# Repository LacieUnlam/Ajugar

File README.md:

# Ajugar

<br>

Ajugar is an electronic circuit based on Makey Makey, but with an easy to build PCB in  KiCad. 
More info at [Ajugar web page](http://www.lacie-unlam.org/dokuwiki/doku.php?id=ajugar_publico).

AjugarV1
--------
  * First version. 
  * Validated in hardware.
  * Made with Kicad 2013.
  
AjugarV2
--------
  * Second version.
  * Cleaner design.
  * Made With Kicad 2015.
  * Not tested yet.

License Information
-------------------
The hardware is released under [Creative Commons ShareAlike 4.0 International](https://creativecommons.org/licenses/by-sa/4.0/).

Distributed as-is; no warranty is given.

You can find more information about them [here](http://www.lacie-unlam.org/).
Original Makey Makey:

  * [Make Makey in Sparkfun](https://www.sparkfun.com/products/11511).
  * [Makey Makey in Github](https://github.com/sparkfun/MaKeyMaKey).
  * [Local copy in this repo](./original/).

Makey Makey is a registered trademark of JoyLabz LLC.

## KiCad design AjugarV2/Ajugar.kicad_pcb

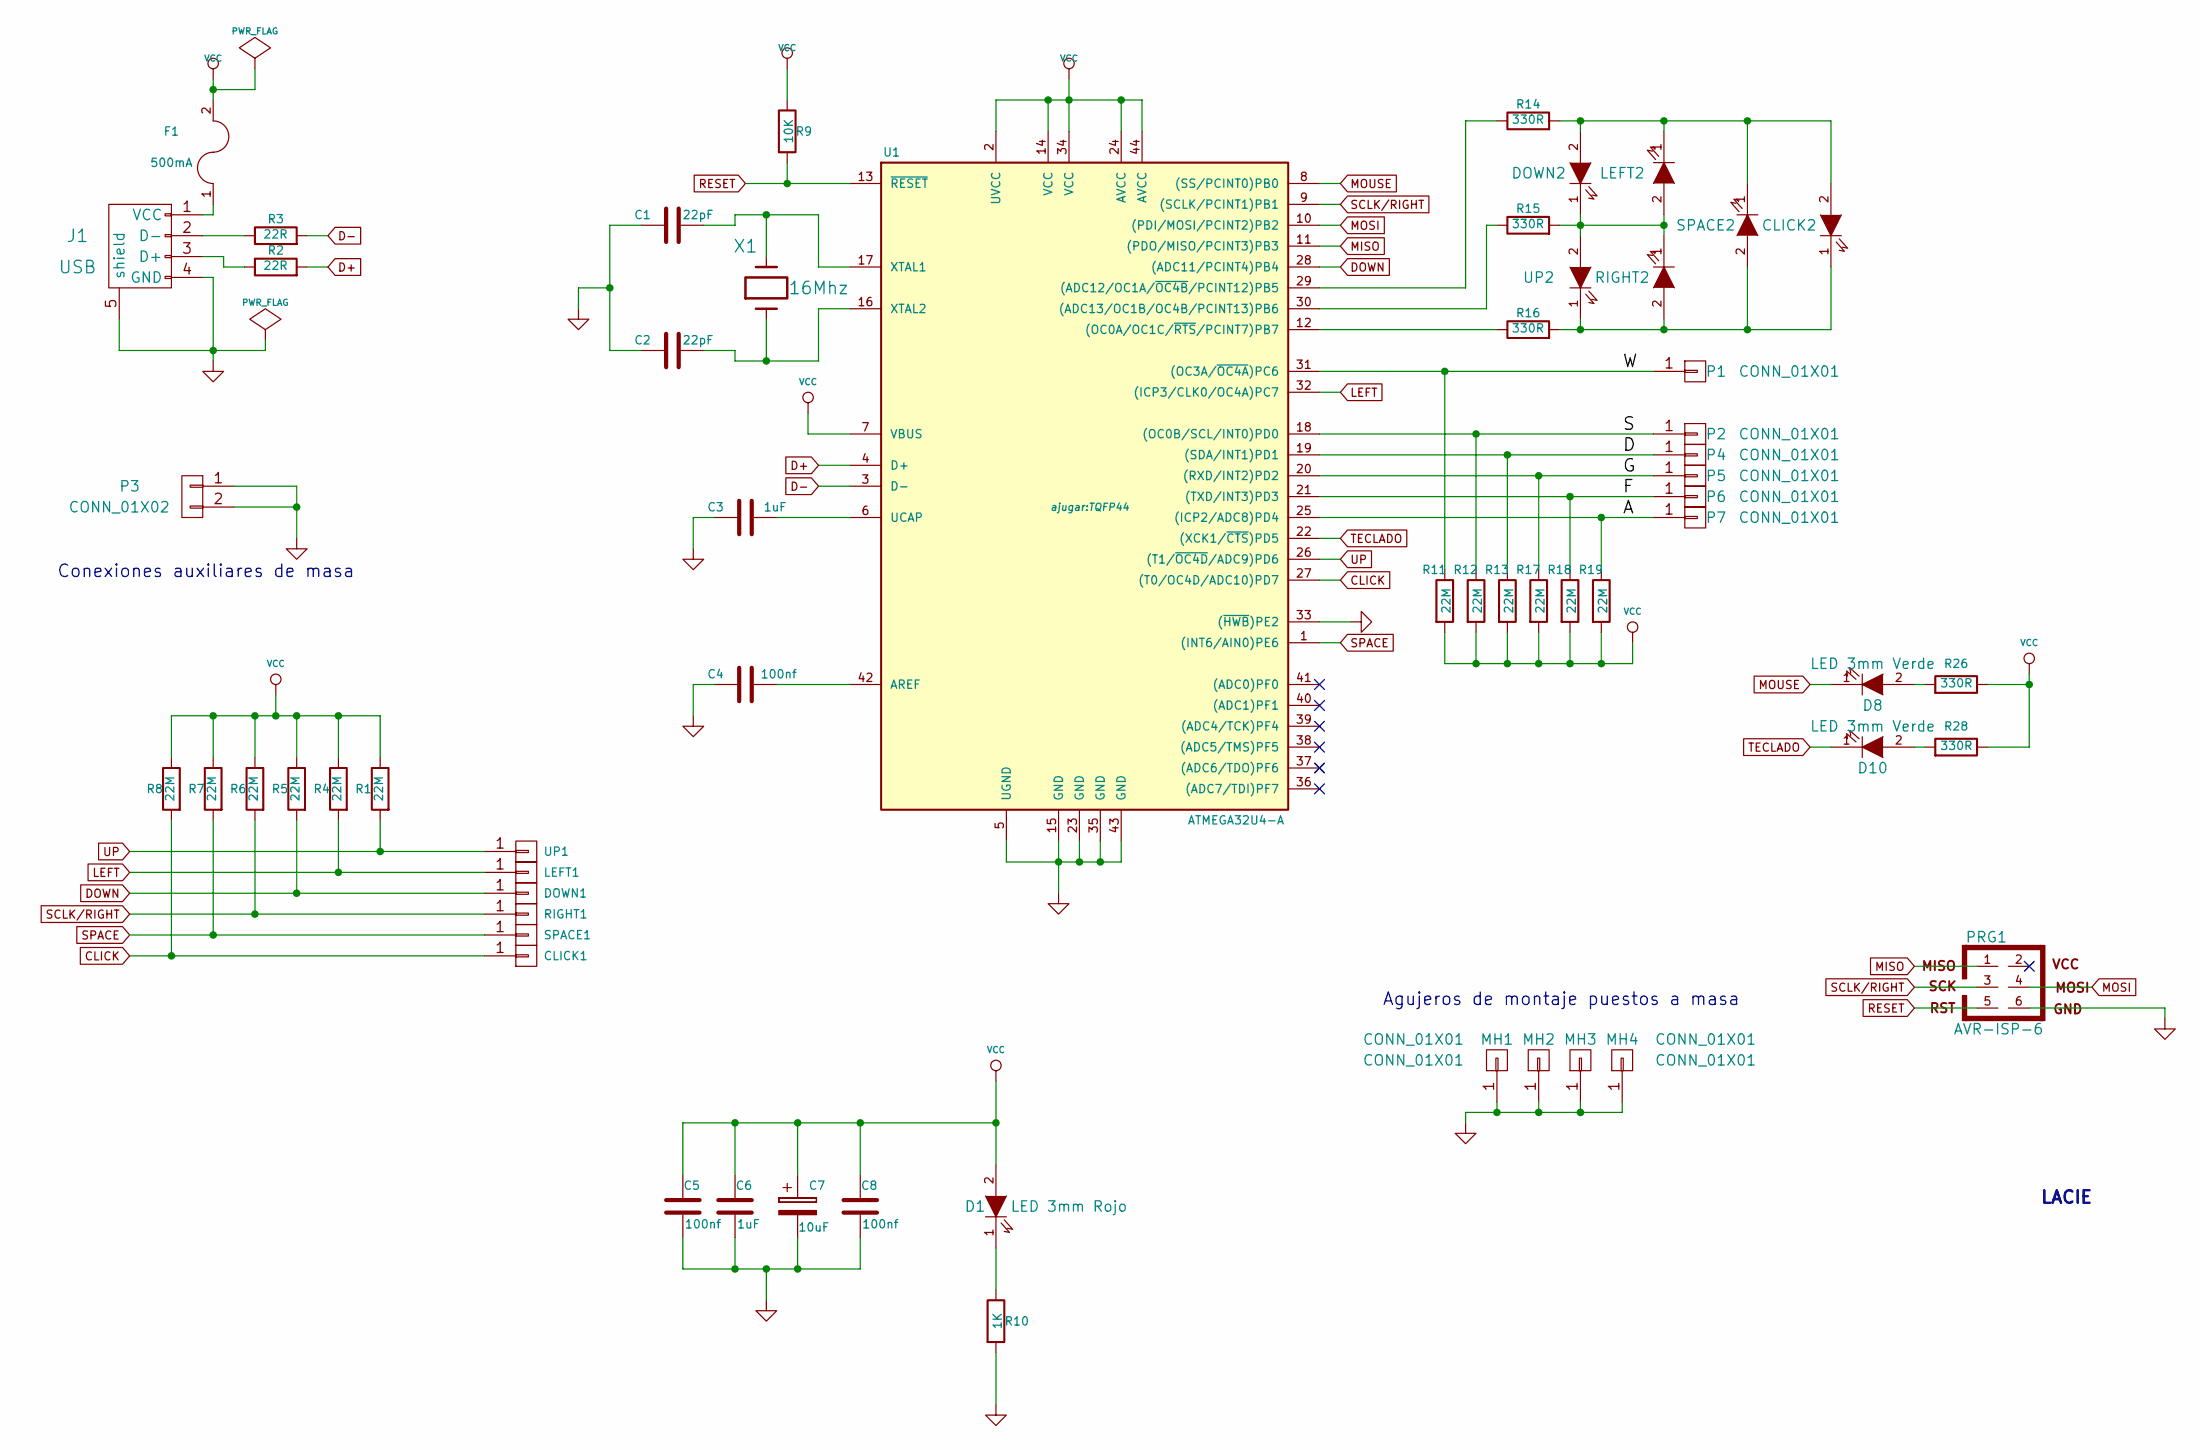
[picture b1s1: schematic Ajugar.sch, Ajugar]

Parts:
C1, C2: 22pF; C1
C3: 1uF; C1
C4, C5, C8: 100nf; C1
C6: 1uF; C1V5
C7: 10uF; C1V5
CLICK1: CONN_1; 1pin
CLICK2: LED 3mm Verde; LED-3MM
D1: LED 3mm Rojo; LED-3MM
D8, D10: LED 3mm Verde; LED-3MM
DOWN1: CONN_1; 1pin
DOWN2: LED 3mm Verde; LED-3MM
F1: 500mA; R4
J1: USB; USB_B
LEFT1: CONN_1; 1pin
LEFT2: LED 3mm Verde; LED-3MM
MH1, MH2, MH3, MH4: CONN_01X01; 1pin
P1, P2, P4, P5, P6, P7: CONN_01X01; 1pin
P3: CONN_01X02; Pin_Header_Straight_1x02
PRG1: AVR-ISP-6; pin_array_3x2
R1, R4, R5, R6, R7, R8, R11, R12, R13, R17, R18, R19: 22M; R3
R2, R3: 22R; R4
R9: 10K; R4
R10: 1K; R4
R14, R15, R28: 330R; R3-5
R16, R26: 330R; R4
RIGHT1: CONN_1; 1pin
RIGHT2: LED 3mm Verde; LED-3MM
SPACE1: CONN_1; 1pin
SPACE2: LED 3mm Verde; LED-3MM
U1: ATMEGA32U4-A; TQFP44
UP1: CONN_1; 1pin
UP2: LED 3mm Verde; LED-3MM
X1: 16Mhz; HC-18UV

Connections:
/A: P7.1, R19.1, U1.25 ((ICP2/ADC8)PD4)
/D: P4.1, R13.1, U1.19 ((SDA/INT1)PD1)
/F: P6.1, R18.1, U1.21 ((TXD/INT3)PD3)
/G: P5.1, R17.1, U1.20 ((RXD/INT2)PD2)
/S: P2.1, R12.1, U1.18 ((OC0B/SCL/INT0)PD0)
/W: P1.1, R11.1, U1.31 ((OC3A/~OC4A~)PC6)
CLICK: CLICK1.1, R8.2, U1.27 ((T0/OC4D/ADC10)PD7)
D+: R2.2, U1.4 (D+)
D-: R3.2, U1.3 (D-)
DOWN: DOWN1.1, R5.2, U1.28 ((ADC11/PCINT4)PB4)
GND: C1.1, C2.1, C3.1, C4.1, C5.2, C6.2, C7.2, C8.2, J1.4 (GND), J1.5 (shield), MH1.1, MH2.1, MH3.1, MH4.1, P3.1, P3.2, PRG1.6, R10.2, U1.5 (UGND), U1.15 (GND), U1.23 (GND), U1.33 ((~HWB~)PE2), U1.35 (GND), U1.43 (GND)
LEFT: LEFT1.1, R4.2, U1.32 ((ICP3/CLK0/OC4A)PC7)
MISO: PRG1.1, U1.11 ((PDO/MISO/PCINT3)PB3)
MOSI: PRG1.4, U1.10 ((PDI/MOSI/PCINT2)PB2)
MOUSE: D8.1 (K), U1.8 ((SS/PCINT0)PB0)
unnamed: C1.2, U1.17 (XTAL1), X1.2
unnamed: C2.2, U1.16 (XTAL2), X1.1
unnamed: C3.2, U1.6 (UCAP)
unnamed: C4.2, U1.42 (AREF)
unnamed: CLICK2.1 (K), R16.2, RIGHT2.2 (A), SPACE2.2 (A), UP2.1 (K)
unnamed: CLICK2.2 (A), DOWN2.2 (A), LEFT2.1 (K), R14.2, SPACE2.1 (K)
unnamed: D1.1 (K), R10.1
unnamed: D8.2 (A), R26.2
unnamed: D10.2 (A), R28.2
unnamed: DOWN2.1 (K), LEFT2.2 (A), R15.2, RIGHT2.1 (K), UP2.2 (A)
unnamed: F1.1, J1.1 (VCC)
unnamed: J1.2 (D-), R3.1
unnamed: J1.3 (D+), R2.1
unnamed: R14.1, U1.29 ((ADC12/OC1A/~OC4B~/PCINT12)PB5)
unnamed: R15.1, U1.30 ((ADC13/OC1B/OC4B/PCINT13)PB6)
unnamed: R16.1, U1.12 ((OC0A/OC1C/~RTS~/PCINT7)PB7)
RESET: PRG1.5, R9.2, U1.13 (~RESET~)
SCLK/RIGHT: PRG1.3, R6.2, RIGHT1.1, U1.9 ((SCLK/PCINT1)PB1)
SPACE: R7.2, SPACE1.1, U1.1 ((INT6/AIN0)PE6)
TECLADO: D10.1 (K), U1.22 ((XCK1/~CTS~)PD5)
UP: R1.2, U1.26 ((T1/~OC4D~/ADC9)PD6), UP1.1
VCC: C5.1, C6.1, C7.1, C8.1, D1.2 (A), F1.2, R1.1, R4.1, R5.1, R6.1, R7.1, R8.1, R9.1, R11.2, R12.2, R13.2, R17.2, R18.2, R19.2, R26.1, R28.1, U1.2 (UVCC), U1.7 (VBUS), U1.14 (VCC), U1.24 (AVCC), U1.34 (VCC), U1.44 (AVCC)

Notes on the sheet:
Agujeros de montaje puestos a masa
Conexiones auxiliares de masa
LACIE

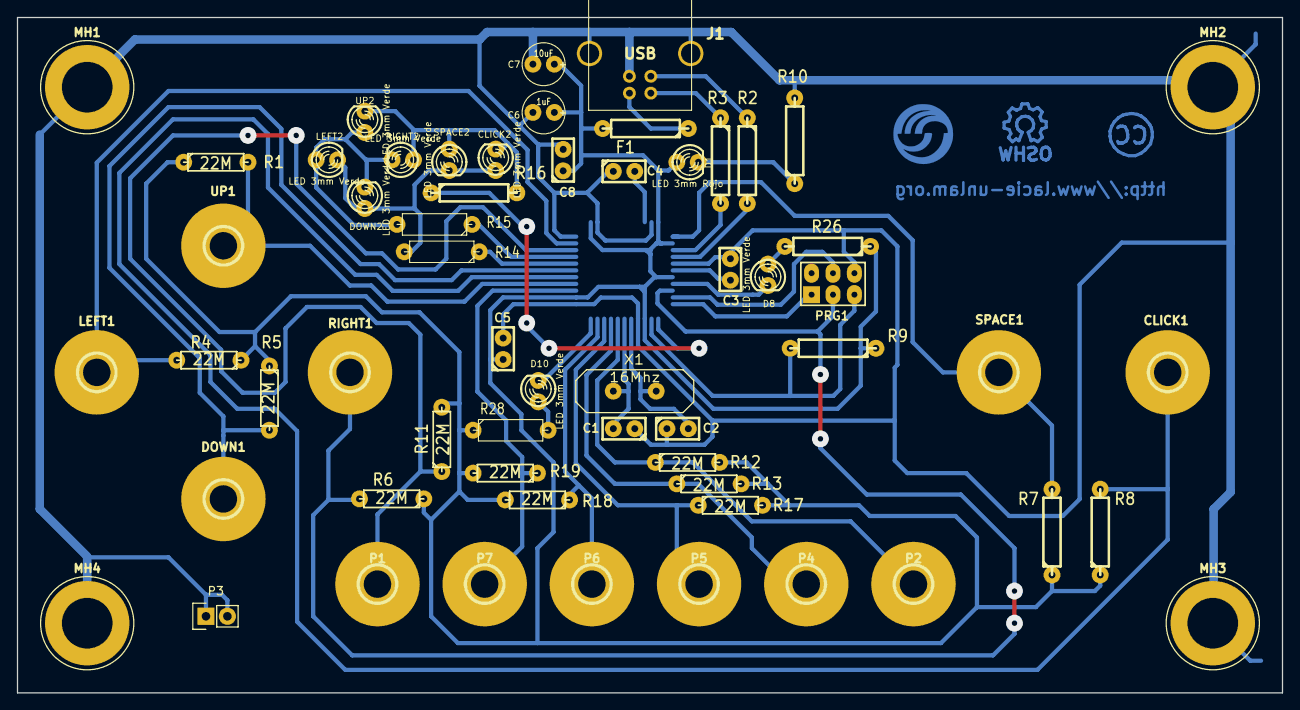
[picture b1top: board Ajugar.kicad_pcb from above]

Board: 2 copper layers, 149.9 x 80.0 mm, 60 parts (1 on the bottom side), 37 nets.

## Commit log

2015-11-06 Added the last version of all project files.
2015-11-06 Minnor changes in README.md
2015-11-06 Title changes and eeschema library cleaning.
2015-11-06 Added .gitignore
2015-11-06 Minnor changes.
2015-11-06 README.md change.
2015-11-06 Update README.md
    Aditional README info.
2015-11-06 Title changes and library organization in V1.
2015-11-06 Added .gitignore to V1.
2015-11-28 Added postscript for AjugarV2 fabrication (2 boards).
2015-12-03 Silkscreen correction.
2015-12-05 Added Top Copper PCBlaye for wires soldering.

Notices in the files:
AjugarV1/Ajugar.sch:
http://creativecommons.org/licenses/by-sa/4.0
Attribution-ShareAlike 4.0 International (CC BY-SA 4.0)
